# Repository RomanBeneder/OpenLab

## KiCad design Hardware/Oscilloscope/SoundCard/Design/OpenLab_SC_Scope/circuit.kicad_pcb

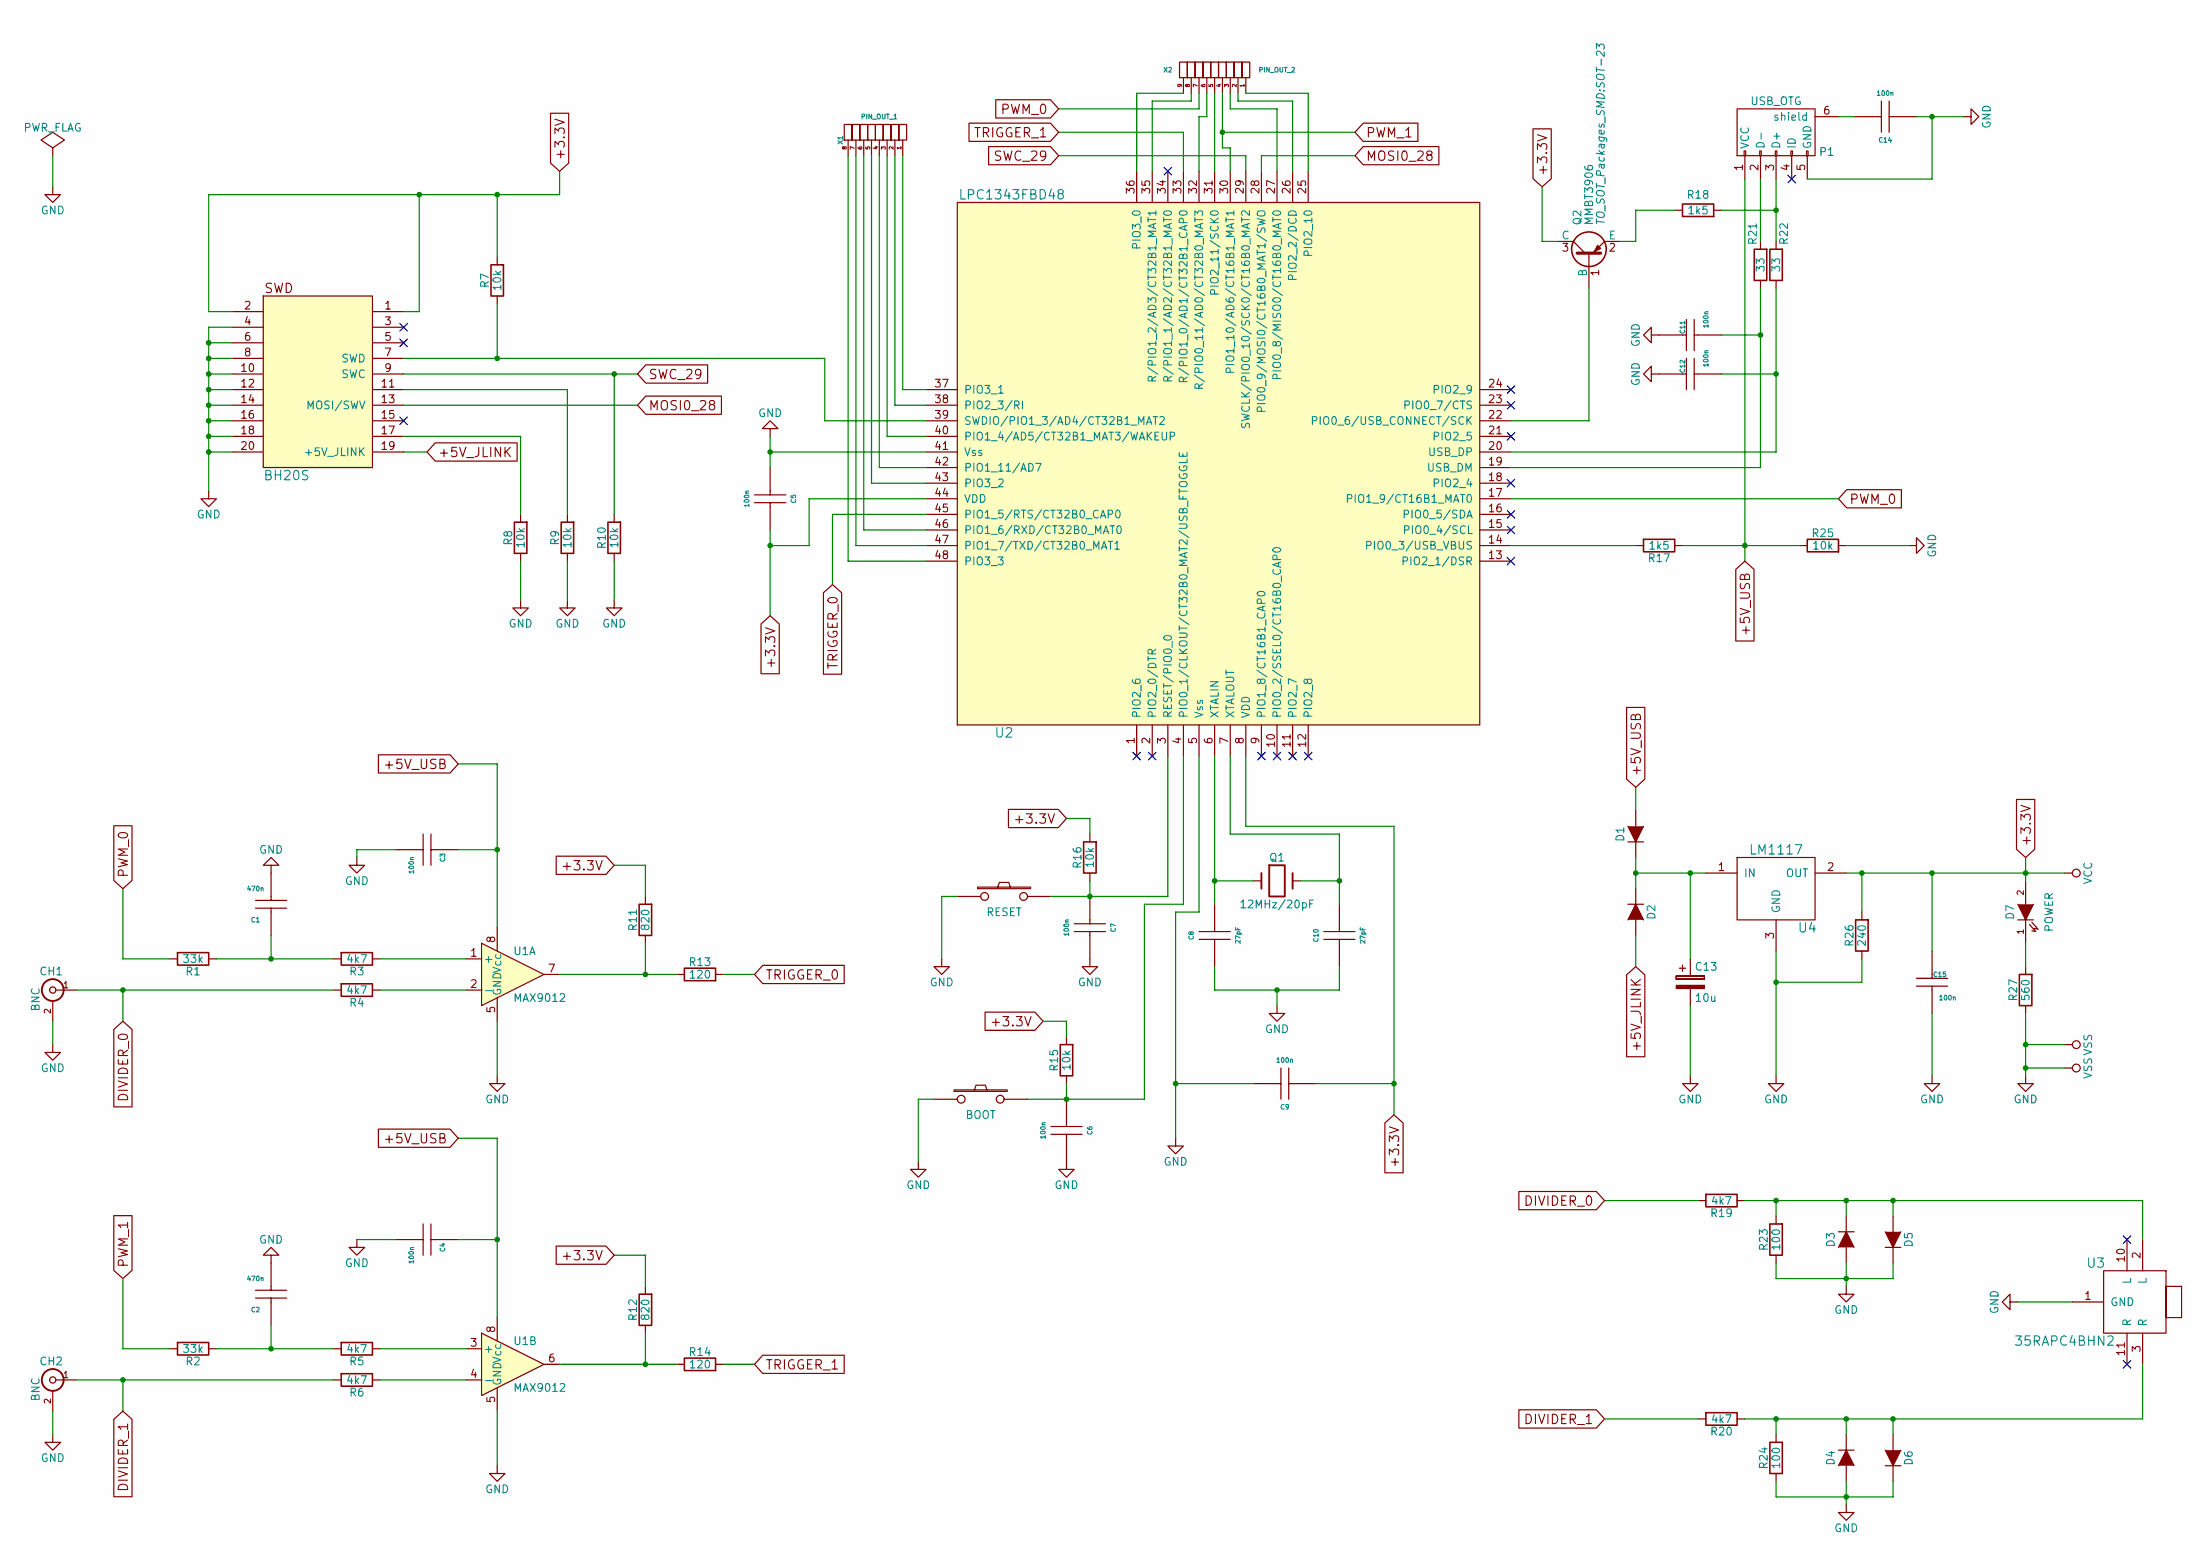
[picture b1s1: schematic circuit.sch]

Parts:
C1, C2: 470n; C_0603
C3, C4, C5, C6, C7, C9, C11, C12, C14, C15: 100n; C_0603
C8, C10: 27pF; C_0603
C13: 10u; c_elec_3x5.3
CH1, CH2: BNC; BNC_Socket_TYCO-AMP_LargePads
D1, D2, D3, D4, D5, D6: DIODE; DO-214BA
D7: POWER; VLMS30K1L2-GS08
P1: USB_OTG; USB_Mini-B
Q1: 12MHz/20pF; Crystal_SMD_0603_2Pads_obsolete
Q2: MMBT3906; SOT-23
R1, R2: 33k; R_0603
R3, R4, R5, R6, R19, R20: 4k7; R_0603
R7, R8, R9, R10, R15, R16, R25: 10k; R_0603
R11, R12: 820; R_0603
R13, R14: 120; R_0603
R17, R18: 1k5; R_0603
R21, R22: 33; R_0603
R23, R24: 100; R_0603
R26: 240; R_0603
R27: 560; R_0603
SW1: BOOT; SW_SPST_EVQQ2
SW2: RESET; SW_SPST_EVQQ2
SWD1: BH20S; Pin_Header_Straight_2x10
U1: MAX9012; SO-8
U2: LPC1343FBD48; LQFP-48_7x7mm_Pitch0.5mm
U3: 35RAPC4BHN2
U4: LM1117; SOT-223
X1: PIN_OUT_1; Pin_Header_Straight_1x08
X2: PIN_OUT_2; Pin_Header_Straight_1x09

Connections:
+3.3V: C5.2, C9.1, C15.1, D7.2 (A), Q2.3 (C), R7.2, R11.2, R12.2, R15.2, R16.2, R26.2, SWD1.1, SWD1.2, U2.8 (VDD), U2.44 (VDD), U4.2 (OUT)
+5V_JLINK: D2.2 (A), SWD1.19 (+5V_JLINK)
+5V_USB: C3.1, C4.1, D1.2 (A), P1.1 (VCC), R17.1, R25.1, U1.8 (Vcc)
DIVIDER_0: CH1.1 (In), R4.2, R19.2
DIVIDER_1: CH2.1 (In), R6.2, R20.2
GND: C1.2, C2.2, C3.2, C4.2, C5.1, C6.2, C7.2, C8.1, C9.2, C10.1, C11.1, C12.1, C13.2, C14.1, C15.2, CH1.2 (Ext), CH2.2 (Ext), D3.2 (A), D4.2 (A), D5.1 (K), D6.1 (K), P1.5 (GND), R8.1, R9.1, R10.1, R23.1, R24.1, R25.2, R26.1, R27.1, SW1.1, SW2.1, SWD1.4, SWD1.6, SWD1.8, SWD1.10, SWD1.12, SWD1.14, SWD1.16, SWD1.18, SWD1.20, U1.5 (GND), U2.5 (Vss), U2.41 (Vss), U3.1 (GND), U4.3 (GND)
MOSI0_28: SWD1.13 (MOSI/SWV), U2.28 (PIO0_9/MOSI0/CT16B0_MAT1/SWO)
unnamed: C1.1, R1.1, R3.2
unnamed: C2.1, R2.1, R5.2
unnamed: C6.1, R15.1, SW1.2, U2.4 (PIO0_1/CLKOUT/CT32B0_MAT2/USB_FTOGGLE)
unnamed: C7.1, R16.1, SW2.2, U2.3 (RESET/PIO0_0)
unnamed: C8.2, Q1.1, U2.6 (XTALIN)
unnamed: C10.2, Q1.2, U2.7 (XTALOUT)
unnamed: C11.2, R21.1, U2.19 (USB_DM)
unnamed: C12.2, R22.1, U2.20 (USB_DP)
unnamed: C13.1, D1.1 (K), D2.1 (K), U4.1 (IN)
unnamed: C14.2, P1.6 (shield)
unnamed: D3.1 (K), D5.2 (A), R19.1, R23.2, U3.2 (L)
unnamed: D4.1 (K), D6.2 (A), R20.1, R24.2, U3.3 (R)
unnamed: D7.1 (K), R27.2
unnamed: P1.2 (D-), R21.2
unnamed: P1.3 (D+), R18.2, R22.2
unnamed: Q2.1 (B), U2.22 (PIO0_6/USB_CONNECT/SCK)
unnamed: Q2.2 (E), R18.1
unnamed: R3.1, U1.1 (+)
unnamed: R4.1, U1.2 (-)
unnamed: R5.1, U1.3 (+)
unnamed: R6.1, U1.4 (-)
unnamed: R7.1, SWD1.7 (SWD), U2.39 (SWDIO/PIO1_3/AD4/CT32B1_MAT2)
unnamed: R8.2, SWD1.17
unnamed: R9.2, SWD1.11
unnamed: R11.1, R13.1, U1.7
unnamed: R12.1, R14.1, U1.6
unnamed: R17.2, U2.14 (PIO0_3/USB_VBUS)
unnamed: U2.25 (PIO2_10), X2.1
unnamed: U2.26 (PIO2_2/DCD), X2.2
unnamed: U2.27 (PIO0_8/MISO0/CT16B0_MAT0), X2.3
unnamed: U2.31 (PIO2_11/SCK0), X2.5
unnamed: U2.32 (R/PIO0_11/AD0/CT32B0_MAT3), X2.6
unnamed: U2.35 (R/PIO1_2/AD3/CT32B1_MAT1), X2.8
unnamed: U2.36 (PIO3_0), X2.9
unnamed: U2.37 (PIO3_1), X1.1
unnamed: U2.38 (PIO2_3/RI), X1.2
unnamed: U2.40 (PIO1_4/AD5/CT32B1_MAT3/WAKEUP), X1.3
unnamed: U2.42 (PIO1_11/AD7), X1.4
unnamed: U2.43 (PIO3_2), X1.5
unnamed: U2.46 (PIO1_6/RXD/CT32B0_MAT0), X1.6
unnamed: U2.47 (PIO1_7/TXD/CT32B0_MAT1), X1.7
unnamed: U2.48 (PIO3_3), X1.8
PWM_0: R1.2, U2.17 (PIO1_9/CT16B1_MAT0), X2.7
PWM_1: R2.2, U2.30 (PIO1_10/AD6/CT16B1_MAT1), X2.4
SWC_29: R10.2, SWD1.9 (SWC), U2.29 (SWCLK/PIO0_10/SCK0/CT16B0_MAT2)
TRIGGER_0: R13.2, U2.45 (PIO1_5/RTS/CT32B0_CAP0)
TRIGGER_1: R14.2, U2.33 (R/PIO1_0/AD1/CT32B1_CAP0)

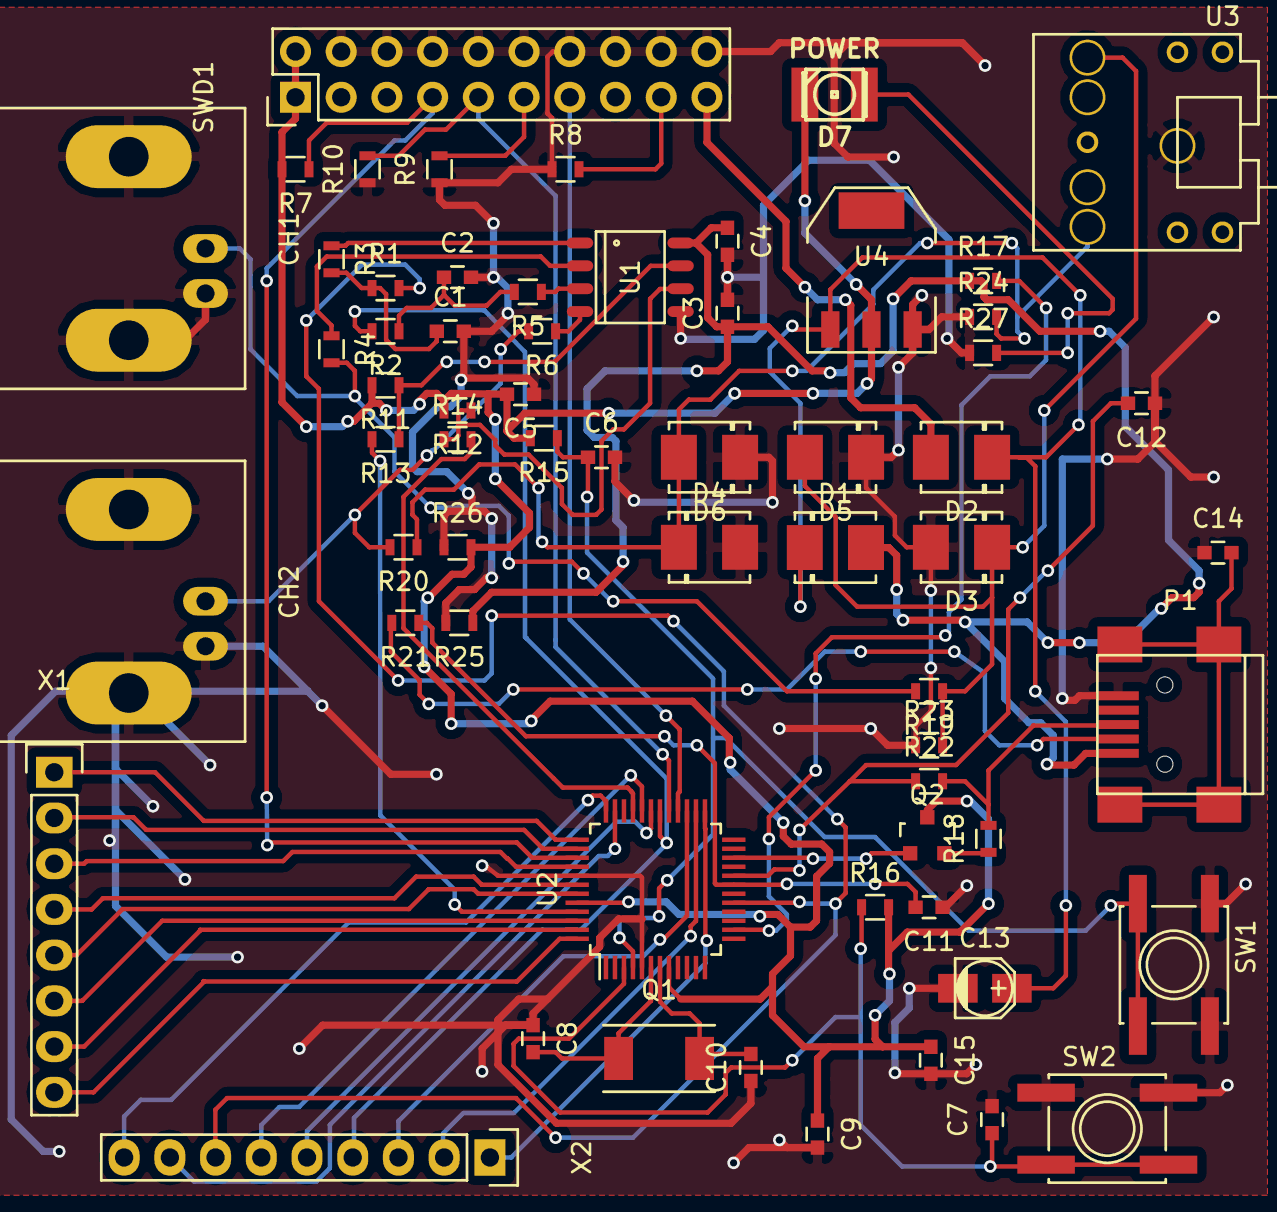
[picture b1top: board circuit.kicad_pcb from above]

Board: 2 copper layers, 63 parts (0 on the bottom side), 54 nets.

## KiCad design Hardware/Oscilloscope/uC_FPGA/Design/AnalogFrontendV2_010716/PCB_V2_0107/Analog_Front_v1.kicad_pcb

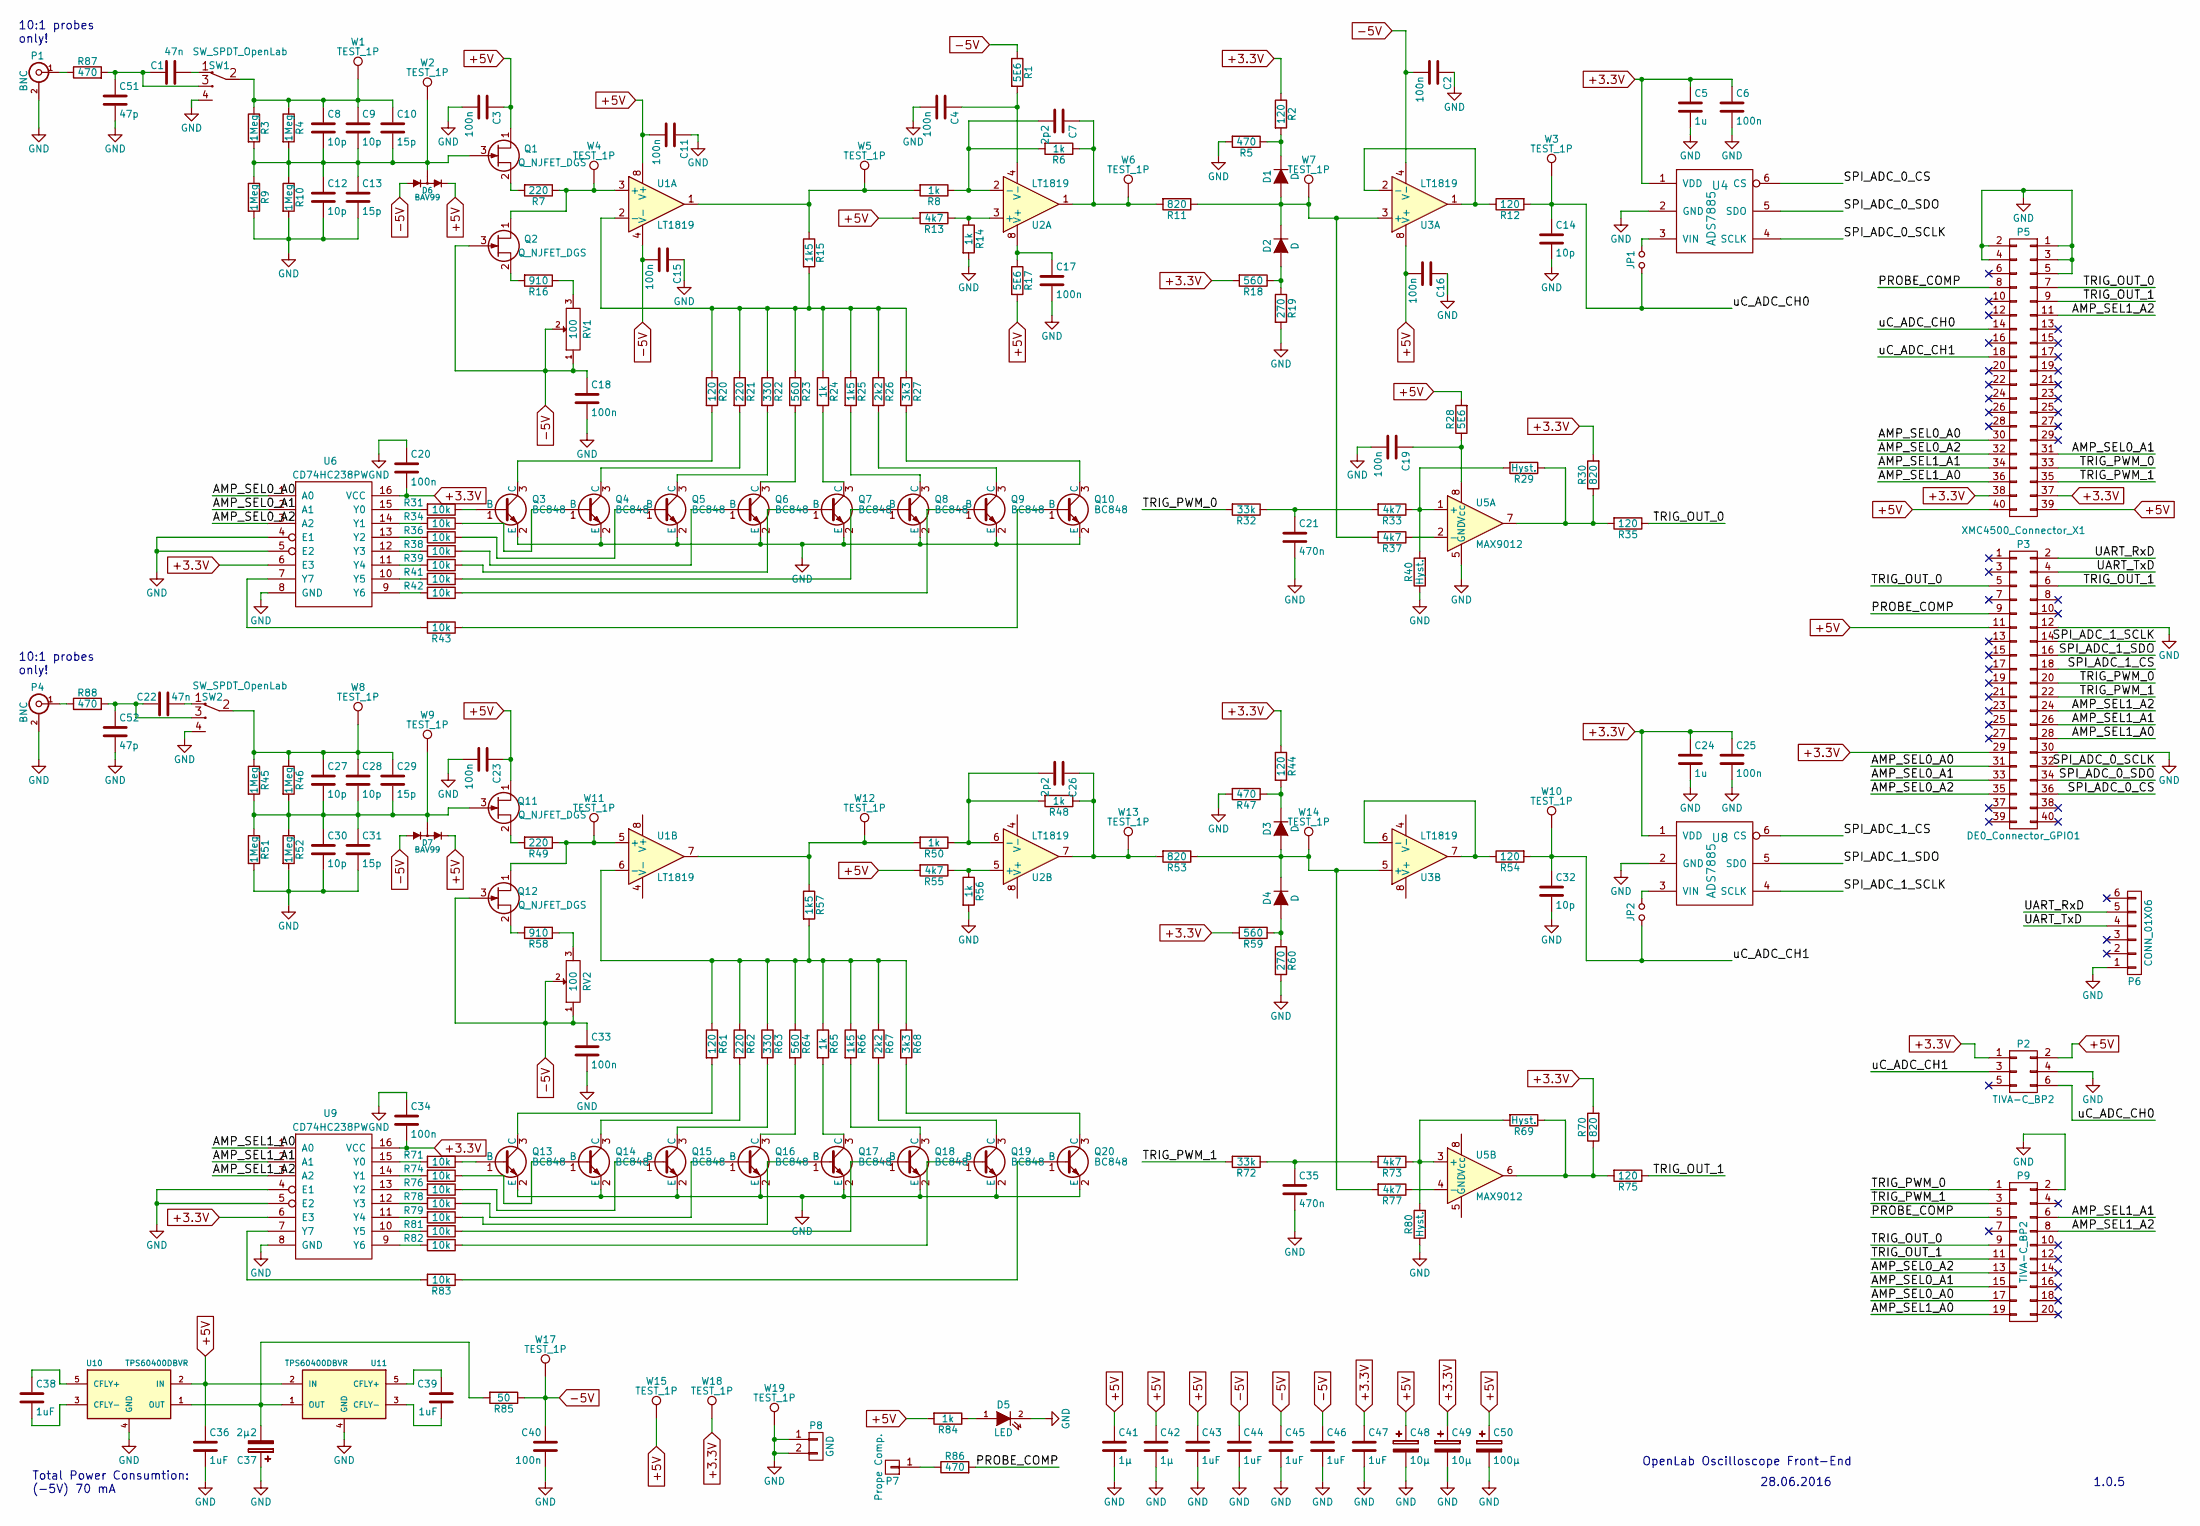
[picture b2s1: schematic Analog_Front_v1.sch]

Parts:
C1, C22: 47n; C_0603
C2, C3, C4, C6, C11, C15, C16, C17, C18, C19, C20, C23, C25, C33, C34, C40: 100n; C_0603
C5, C24: 1u; C_0603
C7, C26: 2p2; C_0603
C8, C9, C12, C14, C27, C28, C30, C32: 10p; C_0603
C10, C13, C29, C31: 15p; C_0603
C21, C35: 470n; C_0603
C36, C38, C39, C43, C44, C45, C46, C47: 1uF; C_0603
C37: 2µ2; c_elec_4x5.3
C41, C42: 1µ; C_0603
C48, C49: 10µ; c_elec_5x5.3
C50: 100µ; c_elec_6.3x5.8
C51, C52: 47p; C_0603
D1, D2, D3, D4: D; SOD-323
D5: LED; LED-0805
D6, D7: BAV99; Diode_SOT23
JP1, JP2: Jumper_NO_Small; R_0603
P1, P4: BNC; BNC_Socket_TYCO-AMP
P2: TIVA-C_BP2; Pin_Header_Straight_2x03
P3: DE0_Connector_GPIO1; Pin_Header_Straight_2x20
P5: XMC4500_Connector_X1; Pin_Header_Straight_2x20
P6: CONN_01X06; Pin_Header_Straight_1x06
P7: Prope Comp.; Pin_Header_Straight_1x01
P8: GND; Pin_Header_Straight_1x02
P9: TIVA-C_BP2; Pin_Header_Straight_2x10
Q1, Q2, Q11, Q12: Q_NJFET_DGS; SOT-23
Q3, Q4, Q5, Q6, Q7, Q8, Q9, Q10, Q13, Q14, Q15, Q16, Q17, Q18, Q19, Q20: BC848; SOT-23
R1, R17, R28: 5E6; R_0603
R2, R12, R20, R35, R44, R54, R61, R75: 120; R_0603
R3, R4, R9, R10, R45, R46, R51, R52: 1Meg; R_0603
R5, R47, R86, R87, R88: 470; R_0603
R6, R8, R14, R24, R48, R50, R56, R65, R84: 1k; R_0603
R7, R21, R49, R62: 220; R_0603
R11, R30, R53, R70: 820; R_0603
R13, R33, R37, R55, R73, R77: 4k7; R_0603
R15, R25, R57, R66: 1k5; R_0603
R16, R58: 910; R_0603
R18, R23, R59, R64: 560; R_0603
R19, R60: 270; R_0603
R22, R63: 330; R_0603
R26, R67: 2k2; R_0603
R27, R68: 3k3; R_0603
R29, R40, R69, R80: Hyst.; R_0603
R31, R34, R36, R38, R39, R41, R42, R43, R71, R74, R76, R78, R79, R81, R82, R83: 10k; R_0603
R32, R72: 33k; R_0603
R85: 50; R_0603
RV1, RV2: 100; TC33X-2-101E
SW1, SW2: SW_SPDT_OpenLab; SWITCH-3-WAY_SPDT
U1, U2, U3: LT1819; SOIC-8_3.9x4.9mm_Pitch1.27mm
U4, U8: ADS7885; TSOT-6-MK06A
U5: MAX9012; SO-8
U6, U9: CD74HC238PW; TSSOP-16_4.4x5mm_Pitch0.65mm
U10, U11: TPS60400DBVR; SOT-23-5
W1, W2, W3, W4, W5, W6, W7, W8, W9, W10, W11, W12, W13, W14, W15, W17, W18, W19: TEST_1P; Measurement_Point_Square-SMD-Pad_Small

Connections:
+3.3V: C5.1, C6.1, C20.2, C24.1, C25.1, C34.2, C47.1, C49.1, P2.1, P3.29, P5.37, P5.38, R2.1, R18.2, R30.2, R44.1, R59.2, R70.2, U4.1 (VDD), U6.6 (E3), U6.16 (VCC), U8.1 (VDD), U9.6 (E3), U9.16 (VCC), W18.1
+5V: C3.1, C11.2, C16.2, C23.1, C36.1, C41.1, C42.1, C43.1, C48.1, C50.1, D6.2 (K), D7.2 (K), P2.2, P3.11, P5.39, P5.40, Q1.1 (D), Q11.1 (D), R13.2, R17.2, R28.2, R55.2, R84.2, U1.8 (V+), U3.8 (V+), U10.2 (IN), U11.2 (IN), W15.1
-5V: C2.2, C15.2, C18.1, C33.1, C40.1, C44.1, C45.1, C46.1, D6.1 (A), D7.1 (A), Q2.3 (G), Q12.3 (G), R1.1, R85.1, RV1.1, RV1.2, RV2.1, RV2.2, U1.4 (V-), U3.4 (V-), W17.1
/AMP_SEL0_A0: P3.31, P5.30, P9.17, U6.1 (A0)
/AMP_SEL0_A1: P3.33, P5.31, P9.15, U6.2 (A1)
/AMP_SEL0_A2: P3.35, P5.32, P9.13, U6.3 (A2)
/AMP_SEL1_A0: P3.28, P5.36, P9.19, U9.1 (A0)
/AMP_SEL1_A1: P3.26, P5.34, P9.6, U9.2 (A1)
/AMP_SEL1_A2: P3.24, P5.11, P9.8, U9.3 (A2)
/PROBE_COMP: P3.9, P5.8, P9.5, R86.2
/SPI_ADC_0_CS: P3.36, U4.6 (CS)
/SPI_ADC_0_SCLK: P3.32, U4.4 (SCLK)
/SPI_ADC_0_SDO: P3.34, U4.5 (SDO)
/SPI_ADC_1_CS: P3.18, U8.6 (CS)
/SPI_ADC_1_SCLK: P3.14, U8.4 (SCLK)
/SPI_ADC_1_SDO: P3.16, U8.5 (SDO)
/TRIG_OUT_0: P3.5, P5.7, P9.9, R35.1
/TRIG_OUT_1: P3.6, P5.9, P9.11, R75.1
/TRIG_PWM_0: P3.20, P5.33, P9.1, R32.2
/TRIG_PWM_1: P3.22, P5.35, P9.3, R72.2
/UART_RxD: P3.2, P6.5
/UART_TxD: P3.4, P6.4
/uC_ADC_CH0: C14.1, JP1.1, P2.6, P5.14, R12.2, W3.1
/uC_ADC_CH1: C32.1, JP2.1, P2.3, P5.18, R54.2, W10.1
GND: C2.1, C3.2, C4.2, C5.2, C6.2, C11.1, C12.2, C13.2, C14.2, C15.1, C16.1, C17.2, C18.2, C19.2, C20.1, C21.2, C23.2, C24.2, C25.2, C30.2, C31.2, C32.2, C33.2, C34.1, C35.2, C36.2, C37.1, C40.2, C41.2, C42.2, C43.2, C44.2, C45.2, C46.2, C47.2, C48.2, C49.2, C50.2, C51.2, C52.2, D5.2 (K), P1.2 (Ext), P2.4, P3.12, P3.30, P4.2 (Ext), P5.1, P5.2, P5.3, P5.4, P5.5, P6.1, P8.1, P8.2, P9.2, Q3.2 (E), Q4.2 (E), Q5.2 (E), Q6.2 (E), Q7.2 (E), Q8.2 (E), Q9.2 (E), Q10.2 (E), Q13.2 (E), Q14.2 (E), Q15.2 (E), Q16.2 (E), Q17.2 (E), Q18.2 (E), Q19.2 (E), Q20.2 (E), R5.2, R9.2, R10.2, R14.2, R19.2, R40.1, R47.2, R51.2, R52.2, R56.2, R60.2, R80.1, SW1.4 (FRAME), SW2.4 (FRAME), U4.2 (GND), U5.5 (GND), U6.4 (E1), U6.5 (E2), U6.8 (GND), U8.2 (GND), U9.4 (E1), U9.5 (E2), U9.8 (GND), U10.4 (GND), U11.4 (GND), W19.1
unnamed: C1.1, SW1.1 (AC)
unnamed: C1.2, C51.1, R87.2, SW1.3 (DC)
unnamed: C4.1, R1.2, U2.4 (V-)
unnamed: C7.1, R6.1, R11.2, U2.1, W6.1
unnamed: C7.2, R6.2, R8.1, U2.2 (-)
unnamed: C8.1, C9.1, C10.1, R3.1, R4.1, SW1.2 (SIG), W1.1
unnamed: C8.2, C9.2, C10.2, C12.1, C13.1, D6.3 (KA), Q1.3 (G), R3.2, R4.2, R9.1, R10.1, W2.1
unnamed: C17.1, R17.1, U2.8 (V+)
unnamed: C19.1, R28.1, U5.8 (Vcc)
unnamed: C21.1, R32.1, R33.2
unnamed: C22.1, SW2.1 (AC)
unnamed: C22.2, C52.1, R88.2, SW2.3 (DC)
unnamed: C26.1, R48.1, R53.2, U2.7, W13.1
unnamed: C26.2, R48.2, R50.1, U2.6 (-)
unnamed: C27.1, C28.1, C29.1, R45.1, R46.1, SW2.2 (SIG), W8.1
unnamed: C27.2, C28.2, C29.2, C30.1, C31.1, D7.3 (KA), Q11.3 (G), R45.2, R46.2, R51.1, R52.1, W9.1
unnamed: C35.1, R72.1, R73.2
unnamed: C37.2, R85.2, U10.1 (OUT), U11.1 (OUT)
unnamed: C38.1, U10.5 (CFLY+)
unnamed: C38.2, U10.3 (CFLY-)
unnamed: C39.1, U11.5 (CFLY+)
unnamed: C39.2, U11.3 (CFLY-)
unnamed: D1.1 (A), D2.2 (K), R11.1, R37.2, U3.3 (+), W7.1
unnamed: D1.2 (K), R2.2, R5.1
unnamed: D2.1 (A), R18.1, R19.1
unnamed: D3.1 (A), D4.2 (K), R53.1, R77.2, U3.5 (+), W14.1
unnamed: D3.2 (K), R44.2, R47.1
unnamed: D4.1 (A), R59.1, R60.1
unnamed: D5.1 (A), R84.1
unnamed: JP1.2, U4.3 (VIN)
unnamed: JP2.2, U8.3 (VIN)
unnamed: P1.1 (In), R87.1
unnamed: P4.1 (In), R88.1
unnamed: P7.1, R86.1
unnamed: Q1.2 (S), R7.2
unnamed: Q2.1 (D), R7.1, U1.3 (+), W4.1
unnamed: Q2.2 (S), R16.2
unnamed: Q3.1 (B), R31.1
unnamed: Q3.3 (C), R20.2
unnamed: Q4.1 (B), R34.1
unnamed: Q4.3 (C), R21.2
unnamed: Q5.1 (B), R36.1
unnamed: Q5.3 (C), R22.2
unnamed: Q6.1 (B), R38.1
unnamed: Q6.3 (C), R23.2
unnamed: Q7.1 (B), R39.1
unnamed: Q7.3 (C), R24.2
unnamed: Q8.1 (B), R41.1
unnamed: Q8.3 (C), R25.2
unnamed: Q9.1 (B), R42.1
unnamed: Q9.3 (C), R26.2
unnamed: Q10.1 (B), R43.1
unnamed: Q10.3 (C), R27.2
unnamed: Q11.2 (S), R49.2
unnamed: Q12.1 (D), R49.1, U1.5 (+), W11.1
unnamed: Q12.2 (S), R58.2
unnamed: Q13.1 (B), R71.1
unnamed: Q13.3 (C), R61.2
unnamed: Q14.1 (B), R74.1
unnamed: Q14.3 (C), R62.2
unnamed: Q15.1 (B), R76.1
unnamed: Q15.3 (C), R63.2
unnamed: Q16.1 (B), R78.1
unnamed: Q16.3 (C), R64.2
unnamed: Q17.1 (B), R79.1
unnamed: Q17.3 (C), R65.2
unnamed: Q18.1 (B), R81.1
unnamed: Q18.3 (C), R66.2
unnamed: Q19.1 (B), R82.1
unnamed: Q19.3 (C), R67.2
unnamed: Q20.1 (B), R83.1
unnamed: Q20.3 (C), R68.2
unnamed: R12.1, U3.1, U3.2 (-)
unnamed: R13.1, R14.1, U2.3 (+)
unnamed: R8.2, R15.1, U1.1, W5.1
unnamed: R15.2, R20.1, R21.1, R22.1, R23.1, R24.1, R25.1, R26.1, R27.1, U1.2 (-)
unnamed: R16.1, RV1.3
unnamed: R29.1, R30.1, R35.2, U5.7
unnamed: R29.2, R33.1, R40.2, U5.1 (+)
unnamed: R31.2, U6.15 (Y0)
unnamed: R34.2, U6.14 (Y1)
unnamed: R36.2, U6.13 (Y2)
unnamed: R37.1, U5.2 (-)
unnamed: R38.2, U6.12 (Y3)
unnamed: R39.2, U6.11 (Y4)
unnamed: R41.2, U6.10 (Y5)
unnamed: R42.2, U6.9 (Y6)
unnamed: R43.2, U6.7 (Y7)
unnamed: R50.2, R57.1, U1.7, W12.1
unnamed: R54.1, U3.6 (-), U3.7
unnamed: R55.1, R56.1, U2.5 (+)
unnamed: R57.2, R61.1, R62.1, R63.1, R64.1, R65.1, R66.1, R67.1, R68.1, U1.6 (-)
unnamed: R58.1, RV2.3
unnamed: R69.1, R70.1, R75.2, U5.6
unnamed: R69.2, R73.1, R80.2, U5.3 (+)
unnamed: R71.2, U9.15 (Y0)
unnamed: R74.2, U9.14 (Y1)
unnamed: R76.2, U9.13 (Y2)
unnamed: R77.1, U5.4 (-)
unnamed: R78.2, U9.12 (Y3)
unnamed: R79.2, U9.11 (Y4)
unnamed: R81.2, U9.10 (Y5)
unnamed: R82.2, U9.9 (Y6)
unnamed: R83.2, U9.7 (Y7)

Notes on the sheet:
OpenLab Oscilloscope Front-End
28.06.2016
1.0.5
10:1 probes only!
Total Power Consumtion: (-5V) 70 mA

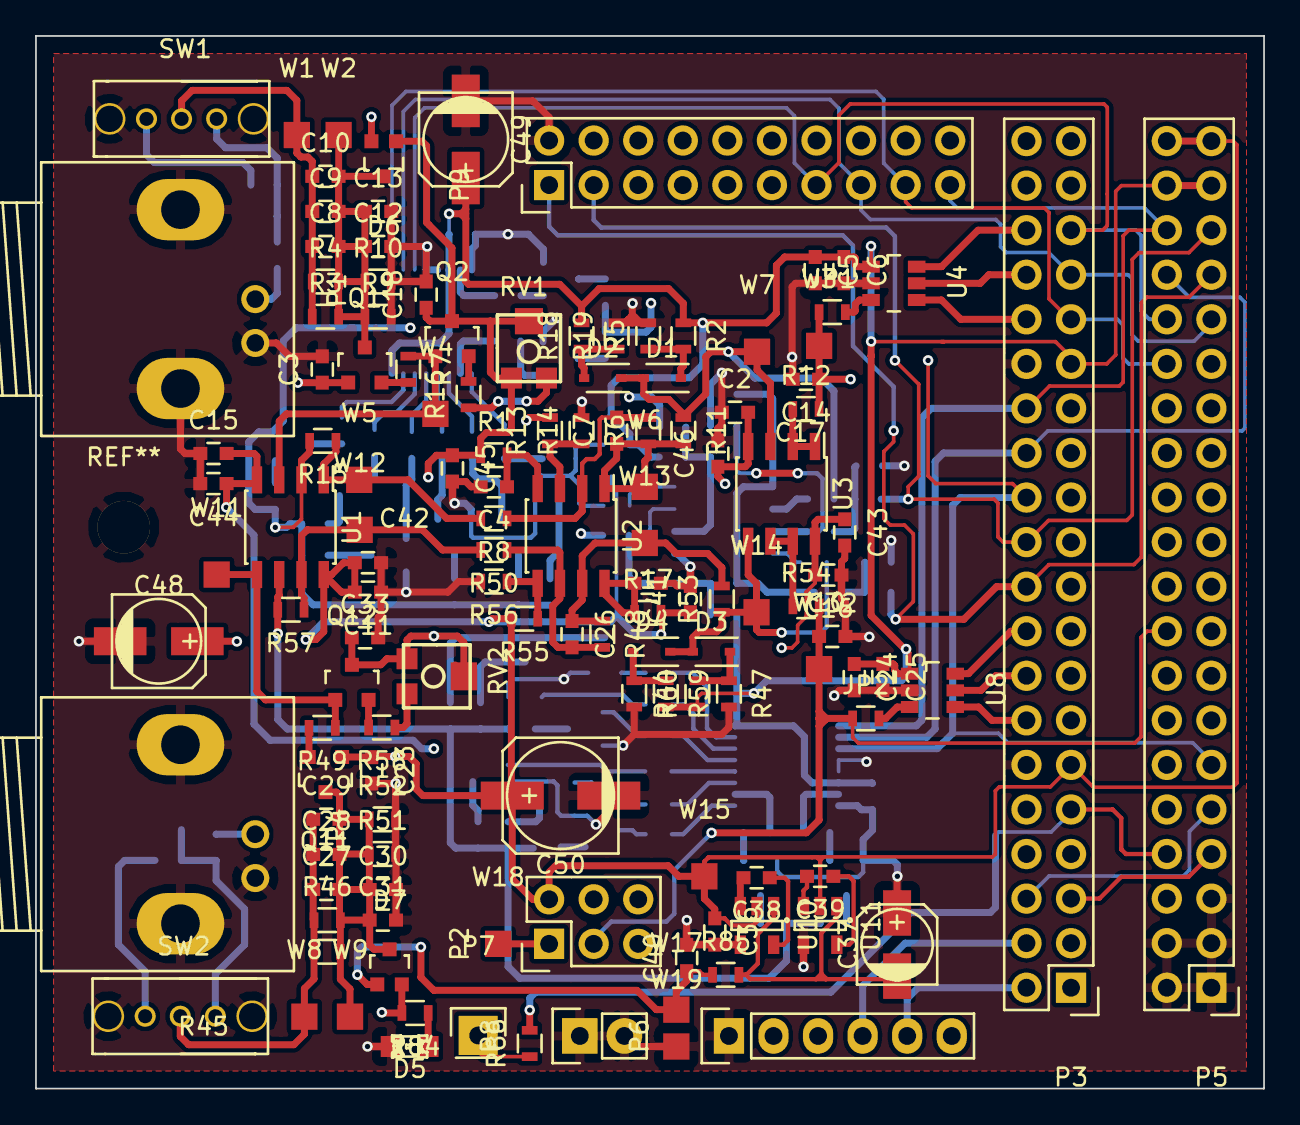
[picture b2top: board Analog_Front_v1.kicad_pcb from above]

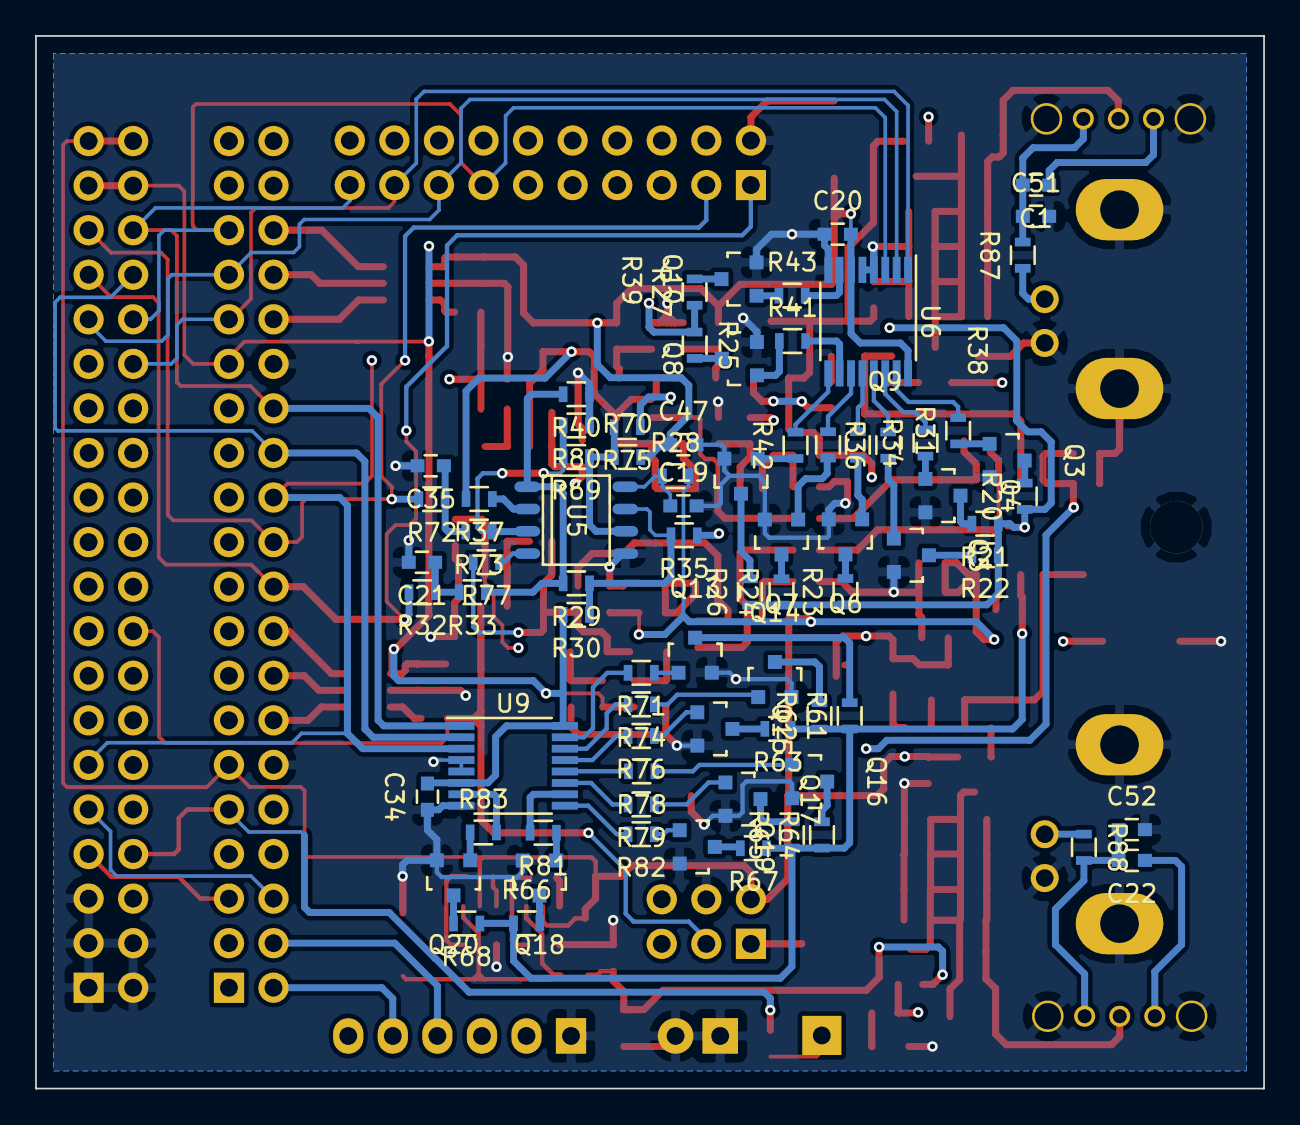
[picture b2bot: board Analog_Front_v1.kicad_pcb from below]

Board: 4 copper layers, 70.0 x 60.0 mm, 210 parts (78 on the bottom side), 129 nets.
